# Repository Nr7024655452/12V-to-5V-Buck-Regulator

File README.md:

# 12V to 5V Buck Regulator (TPS56339) - 

A compact synchronous step-down (buck) converter PCB based on the Texas Instruments **TPS56339**, converting a 12 V input to a regulated 5 V output at up to 3 A.

## Specifications

| Parameter        | Value               |
|------------------|---------------------|
| Input voltage    | 12 V DC             |
| Output voltage   | 5 V                 |
| Output current   | 2 to 3 A            |
| Controller IC    | TPS56339DDCT        |
| Inductor         | 5.6 µH              |
| Input capacitors | 2 x 10 µF + 0.1 µF  |
| Output capacitors| 2 x 22 µF           |
| Connectors       | 2-pin screw terminals |

## Circuit Description

- **J1**: 12 V input screw terminal (with PWR_FLAG)
- **J2**: 5 V output screw terminal
- **U1 (TPS56339)**: Step-down converter IC
- **L1 (5.6 µH)**: Power inductor on the SW node
- **R4 / R5 / R6**: Feedback network setting the output voltage
- **R1 / R2**: Divider on EN pin (input undervoltage lockout)
- **C4 (0.1 µF) + R3**: Bootstrap capacitor and series resistor on the BOOT pin
- **C1, C2, C3**: Input capacitors
- **C5, C6**: Output capacitors

## Repository Structure

## Getting Started

1. Install [KiCad](https://www.kicad.org/) (v7 or later recommended)
2. Open `hardware/<project>.kicad_pro`
3. Generate Gerbers via **File → Fabrication Outputs → Gerbers**

## Usage

1. Connect a 12 V supply to **J1** (check polarity)
2. Measure 5 V at **J2**
3. Do not exceed the rated current without proper cooling

## Notes

- Verify the feedback resistor values against the TPS56339 datasheet for exactly 5.0 V output
- Keep the input capacitors close to the VIN and GND pins
- Keep the SW node and inductor trace short and wide

## Status

- [x] Schematic
- [x] PCB layout
- [ ] Prototype tested

## License

MIT License. See [LICENSE](LICENSE).

## Author

Nitin Rajput: [GitHub](https://github.com/NR7024655452)

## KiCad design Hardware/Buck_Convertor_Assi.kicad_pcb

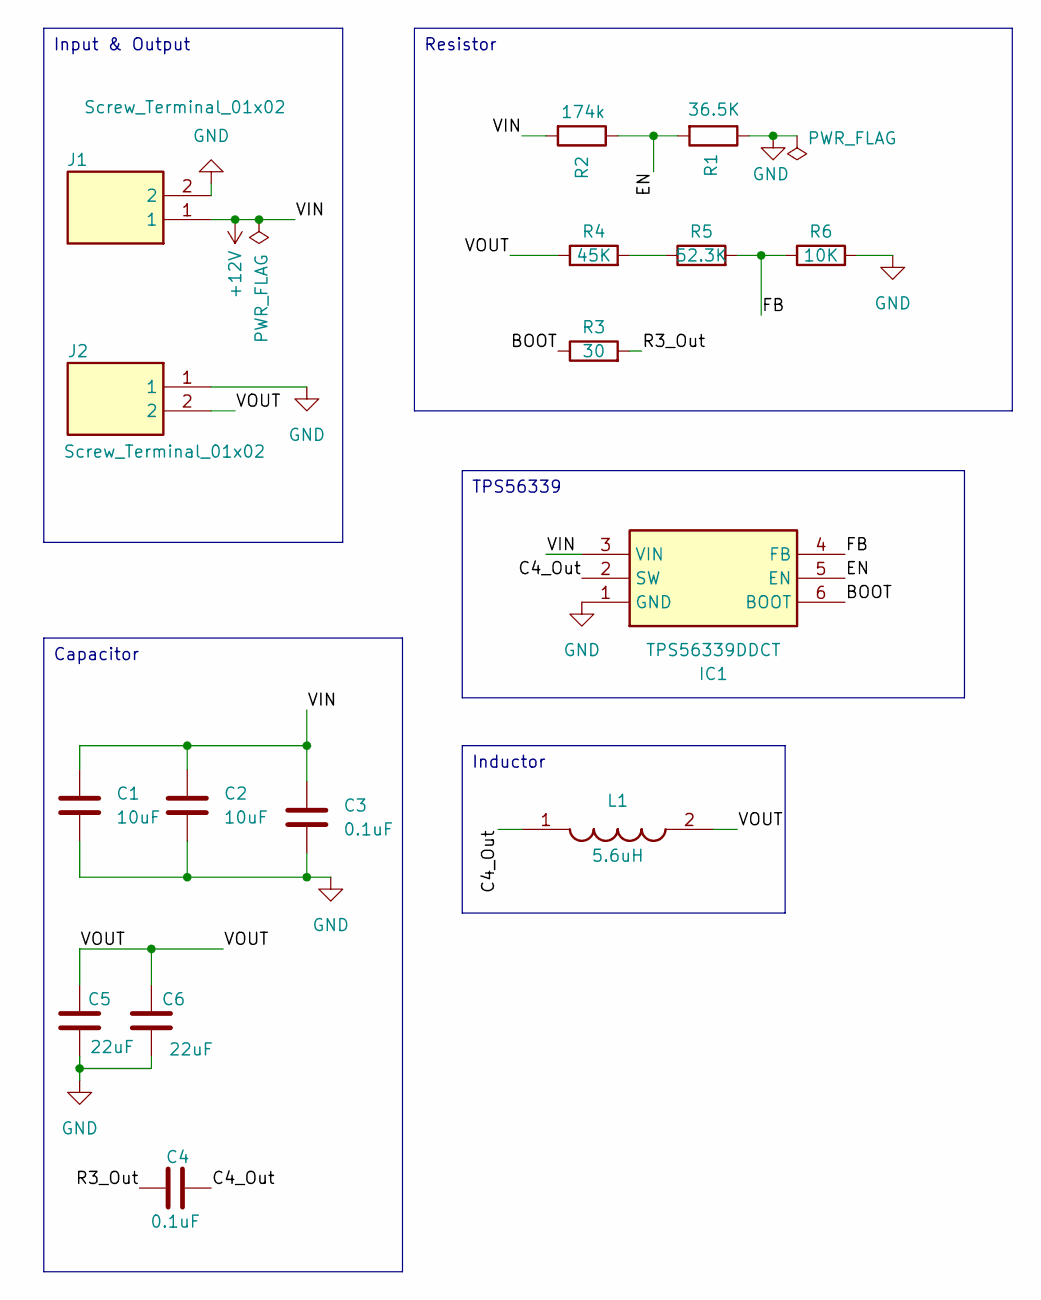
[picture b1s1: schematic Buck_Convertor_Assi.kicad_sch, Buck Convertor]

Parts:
C1, C2: 10uF; C_0805_2012Metric
C3, C4: 0.1uF; C_0805_2012Metric
C5, C6: 22uF; C_0805_2012Metric
IC1: TPS56339DDCT; SOT95P280X110-6N; Mouser Part Number 595-TPS56339DDCT
J1, J2: Screw_Terminal_01x02; SHDR2W100P0X500_1X2_1000X760X1040P; Mouser Part Number 538-39543-0602
L1: 5.6uH; INDM5653X400N; Mouser Part Number 710-744316560
R1: 36.5K; R_0805_2012Metric
R2: 174k; R_0805_2012Metric
R3: 30; R_0805_2012Metric
R4: 45K; R_0805_2012Metric
R5: 52.3K; R_0805_2012Metric
R6: 10K; R_0805_2012Metric

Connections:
+12V: C1.1, C2.1, C3.1, IC1.3 (VIN), J1.1, R2.2
/BOOT: IC1.6 (BOOT), R3.1
/C4_Out: C4.2, IC1.2 (SW), L1.1
/EN: IC1.5 (EN), R1.2, R2.1
/FB: IC1.4 (FB), R5.2, R6.1
/R3_Out: C4.1, R3.2
/VOUT: C5.2, C6.2, J2.2, L1.2, R4.1
GND: C1.2, C2.2, C3.2, C5.1, C6.1, IC1.1 (GND), J1.2, J2.1, R1.1, R6.2
unnamed: R4.2, R5.1

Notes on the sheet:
TPS56339
Resistor
Capacitor
Input & Output
Inductor

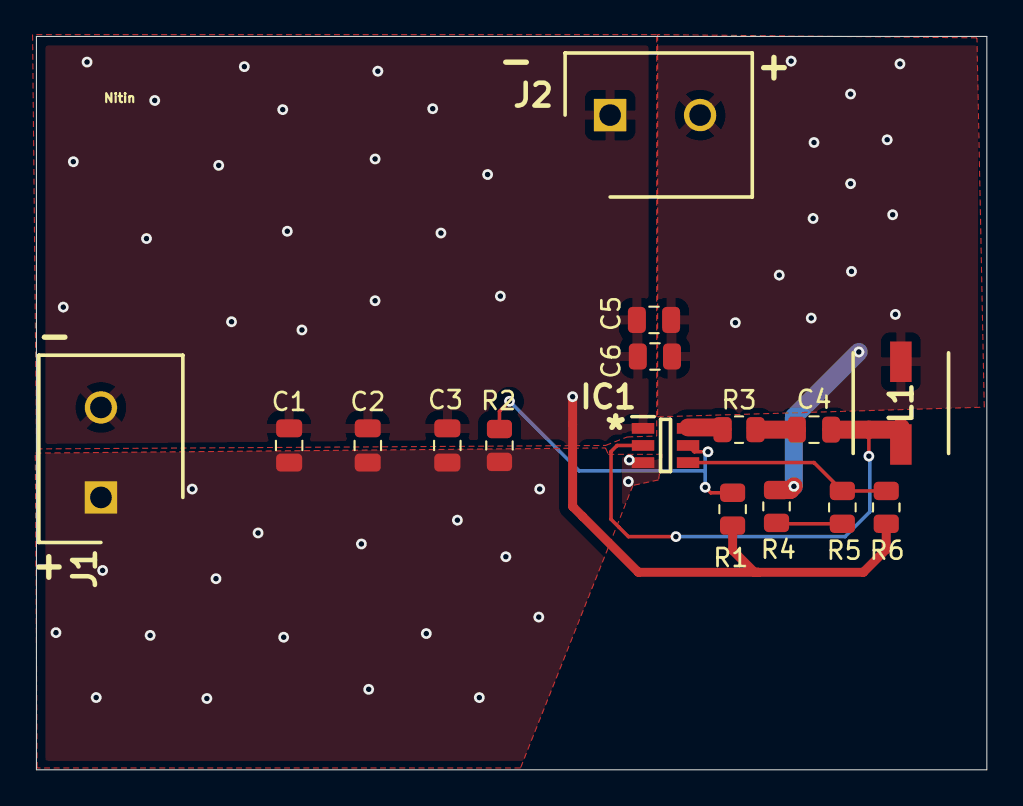
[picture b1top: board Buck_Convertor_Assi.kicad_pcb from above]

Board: 2 copper layers, 52.8 x 40.7 mm, 16 parts (0 on the bottom side), 9 nets.
